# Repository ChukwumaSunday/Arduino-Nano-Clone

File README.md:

# Arduino-Nano-Clone
This project is recreating Arduino Nano development from bare minimum using Eagle CADSoft

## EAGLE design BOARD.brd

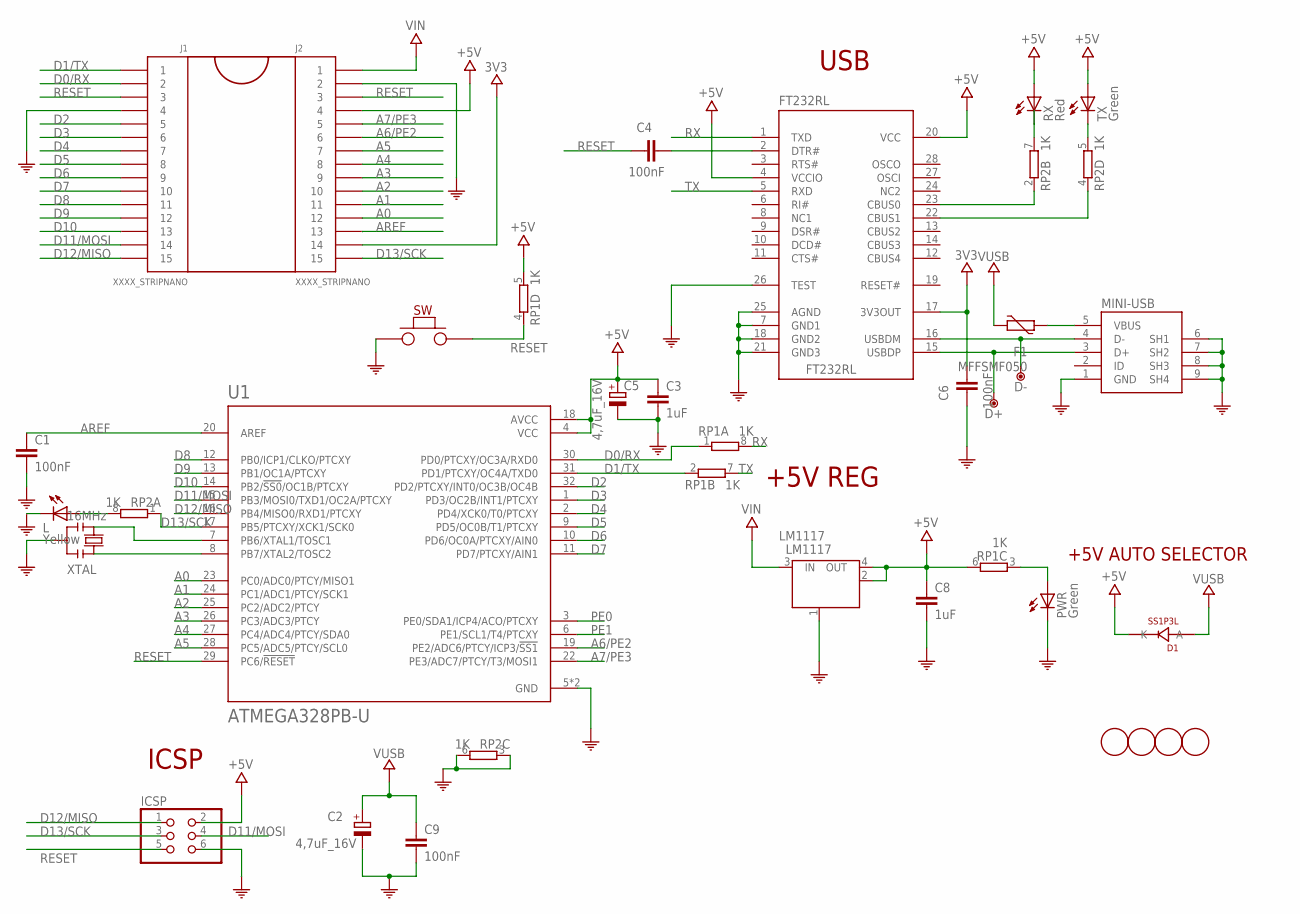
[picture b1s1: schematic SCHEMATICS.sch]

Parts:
C1, C4, C6, C9: 100nF; C0603-ROUND
C2, C5: 4,7uF_16V; TAN-A
C3, C8: 1uF; C0603-ROUND
D1: SS1P3L; DO220AAL
D+: DNP; TP-1.00MM
D-: DNP; TP-1.00MM
F1: MFFSMF050; 0603-1608X90N
FT232RL: FT232RL; SSOP28
ICSP: 0114_PH254-203DF118A00V; 2X03
J1, J2: XXXX_STRIPNANO; HEAD15-NOSS
L: Yellow; CHIPLED_0805
LM1117: LM1117; LINEAR_SOT223
MINI-USB: 0219_14850; USB-MINI-B_2
P0INT_2: DNP; FD-1-1.5
POINT_1: DNP; FD-1-1.5
POINT_A: DNP; FD-1-1.5
POINT_B: DNP; FD-1-1.5
PWR: Green; CHIPLED_0805
RP1, RP2: 1K; CAY16
RX: Red; CHIPLED_0805
TX: Green; CHIPLED_0805
U1: ATMEGA328PB-U; QFP80P900X900X120-32N
U$4: 3*6*4.2H260g; 3*6*4.3_PUSH_SWITCH
XTAL: 16MHz; RESONATOR

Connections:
3V3: C6.2, FT232RL.17 (3V3OUT), J2.14
+5V: C3.1, C5.1 (+), C8.1, D1.P$1 (K), FT232RL.4 (VCCIO), FT232RL.20 (VCC), ICSP.2, J2.4, LM1117.2 (OUT), LM1117.4 (OUT), RP1.5 (2), RP1.6 (2), RX.A, TX.A, U1.4 (VCC), U1.18 (AVCC)
A0: J2.12, U1.23 (PC0/ADC0/PTCY/MISO1)
A1: J2.11, U1.24 (PC1/ADC1/PTCY/SCK1)
A2: J2.10, U1.25 (PC2/ADC2/PTCY)
A3: J2.9, U1.26 (PC3/ADC3/PTCY)
A4: J2.8, U1.27 (PC4/ADC4/PTCY/SDA0)
A5: J2.7, U1.28 (PC5/ADC5/PTCY/SCL0)
A6/PE2: J2.6, U1.19 (PE2/ADC6/PTCY/ICP3/!SS1)
A7/PE3: J2.5, U1.22 (PE3/ADC7/PTCY/T3/MOSI1)
AREF: C1.1, J2.13, U1.20 (AREF)
COM: C1.2, C2.2 (-), C3.2, C5.2 (-), C6.1, C8.2, C9.2, FT232RL.7 (GND1), FT232RL.18 (GND2), FT232RL.21 (GND3), FT232RL.25 (AGND), FT232RL.26 (TEST), ICSP.6, J1.4, J2.2, L.C, LM1117.1 (GND/ADJ), MINI-USB.1 (GND), MINI-USB.6 (SH1), MINI-USB.7 (SH2), MINI-USB.8 (SH3), MINI-USB.9 (SH4), PWR.C, RP2.3 (1), RP2.6 (2), U1.5 (GND), U1.21 (GND), U$4.P$1, XTAL.2
D0/RX: J1.2, RP1.1, U1.30 (PD0/PTCXY/OC3A/RXD0)
D1/TX: J1.1, RP1.2 (1), U1.31 (PD1/PTCXY/OC4A/TXD0)
D2: J1.5, U1.32 (PD2/PTCXY/INT0/OC3B/OC4B)
D3: J1.6, U1.1 (PD3/OC2B/INT1/PTCXY)
D4: J1.7, U1.2 (PD4/XCK0/T0/PTCXY)
D5: J1.8, U1.9 (PD5/OC0B/T1/PTCXY)
D6: J1.9, U1.10 (PD6/OC0A/PTCXY/AIN0)
D7: J1.10, U1.11 (PD7/PTCXY/AIN1)
D8: J1.11, U1.12 (PB0/ICP1/CLKO/PTCXY)
D9: J1.12, U1.13 (PB1/OC1A/PTCXY)
D10: J1.13, U1.14 (PB2/!SS0!/OC1B/PTCXY)
D11/MOSI: ICSP.4, J1.14, U1.15 (PB3/MOSI0/TXD1/OC2A/PTCXY)
D12/MISO: ICSP.1, J1.15, U1.16 (PB4/MISO0/RXD1/PTCXY)
D13/SCK: ICSP.3, J2.15, RP2.1, U1.17 (PB5/PTCXY/XCK1/SCK0)
unnamed: U1.7 (PB6/XTAL1/TOSC1), XTAL.3
unnamed: U1.8 (PB7/XTAL2/TOSC2), XTAL.1
unnamed: PWR.A, RP1.3 (1)
unnamed: C4.2, FT232RL.2 (DTR#)
unnamed: D+.X, FT232RL.15 (USBDP), MINI-USB.3 (D+)
unnamed: D-.X, FT232RL.16 (USBDM), MINI-USB.4 (D-)
unnamed: L.A, RP2.8 (2)
unnamed: FT232RL.23 (CBUS0), RP2.2 (1)
unnamed: FT232RL.22 (CBUS1), RP2.4 (1)
unnamed: RP2.5 (2), TX.C
unnamed: F1.2, MINI-USB.5 (VBUS)
unnamed: RP2.7 (2), RX.C
PE0: U1.3 (PE0/SDA1/ICP4/ACO/PTCXY)
PE1: U1.6 (PE1/SCL1/T4/PTCXY)
RESET: C4.1, ICSP.5, J1.3, J2.3, RP1.4 (1), U1.29 (PC6/!RESET), U$4.P$2
RX: FT232RL.1 (TXD), RP1.8 (2)
TX: FT232RL.5 (RXD), RP1.7 (2)
VIN: J2.1, LM1117.3 (IN)
VUSB: C2.1 (+), C9.1, D1.P$2 (A), F1.1

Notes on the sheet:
+5V REG
ICSP
USB
+5V AUTO SELECTOR

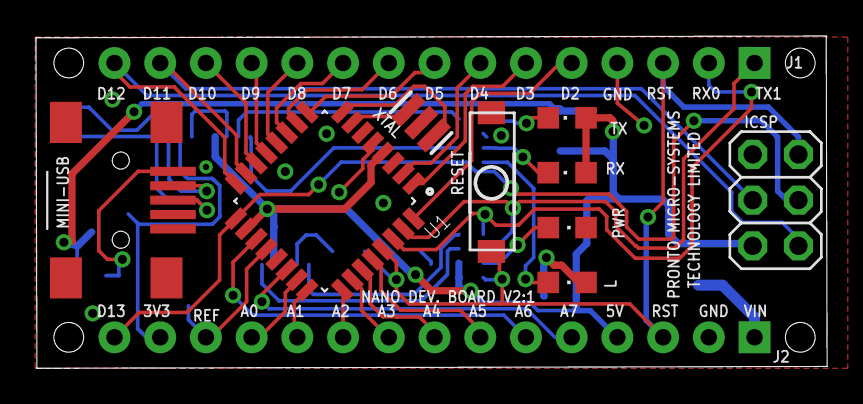
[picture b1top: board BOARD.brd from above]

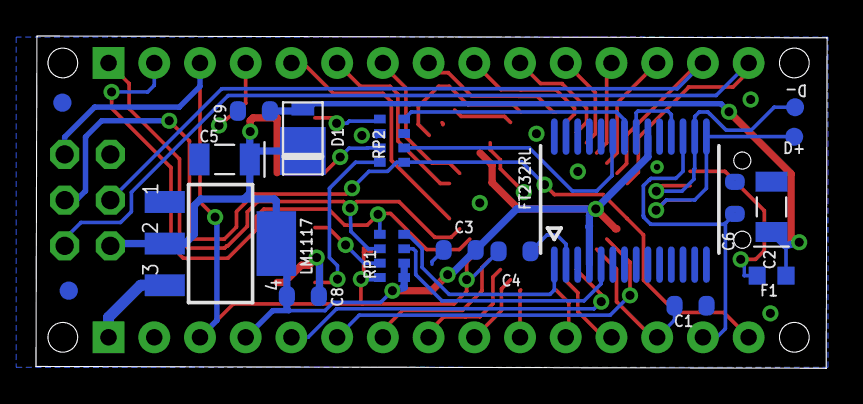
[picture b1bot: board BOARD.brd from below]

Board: 2 copper layers, 43.9 x 18.5 mm, 31 parts (16 on the bottom side), 43 nets.

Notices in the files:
parts and their libraries:
Arduino-utility: Copyright (c) 2016-2017 Arduino LLC.  All right reserved.
